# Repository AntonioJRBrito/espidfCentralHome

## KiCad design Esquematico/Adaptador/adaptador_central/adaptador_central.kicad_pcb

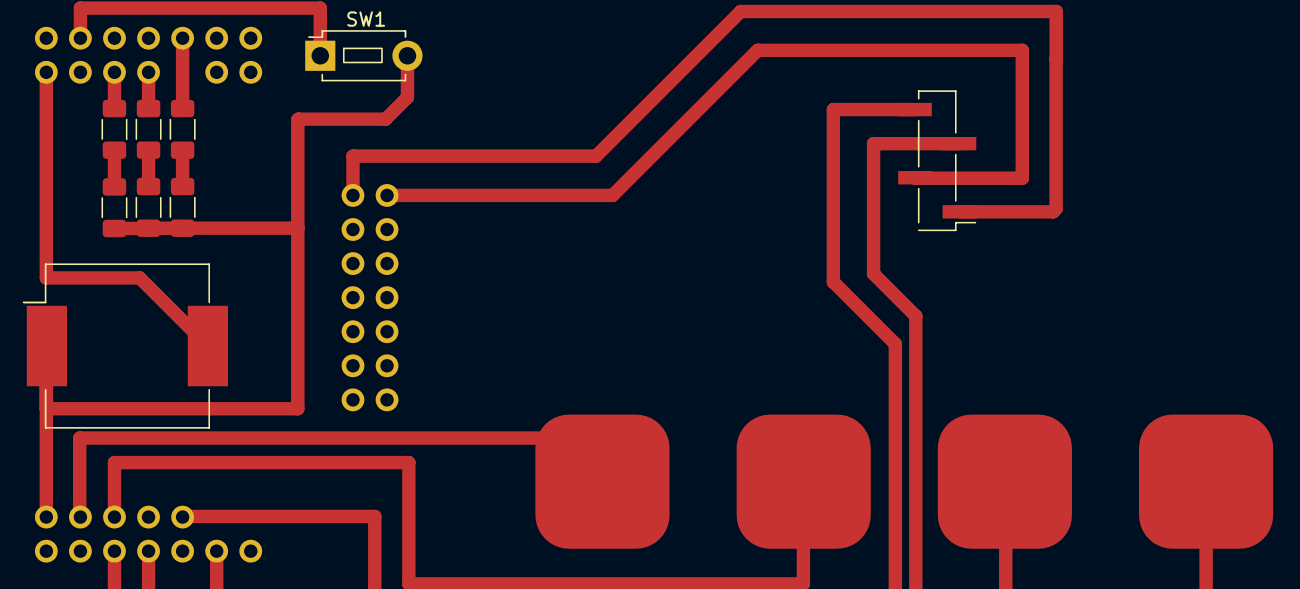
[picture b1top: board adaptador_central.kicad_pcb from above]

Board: 2 copper layers, 11 parts (0 on the bottom side), 16 nets.

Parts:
BZ1: Buzzer; Buzzer_Mallory_AST1240MLQ
Brd1: SSD1306; PinHeader_1x04_P2.54mm_Vertical_SMD_Pin1Left
D1, D2, D3: LED; R_1206_3216Metric_Pad1.30x1.75mm_HandSolder
Jtouch1: Conn_01x04_Pin; touch
R1, R2, R3: R; R_1206_3216Metric_Pad1.30x1.75mm_HandSolder
SW1: SW_MEC_5G; SW_PUSH_1P1T_6x3.5mm_H5.0_APEM_MJTP1250
U1: ESP32-S3-WROOM-1; ESP_S3_dual_suport

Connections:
unnamed: BZ1.1 (+), Brd1.2 (VCC), D1.2 (A), D2.2 (A), D3.2 (A), SW1.2 (A), U1.2 (3V3)
unnamed: BZ1.2 (-), U1.39 (GPIO1/TOUCH1/ADC1_CH0)
unnamed: Brd1.1 (GND), U1.1 (GND), U1.40 (GND)
unnamed: Brd1.3 (SCL), U1.11 (GPIO18/U1RXD/ADC2_CH7/CLK_OUT3)
unnamed: Brd1.4 (SDA), U1.10 (GPIO17/U1TXD/ADC2_CH6)
unnamed: D1.1 (K), R1.2
unnamed: D2.1 (K), R2.2
unnamed: D3.1 (K), R3.2
unnamed: Jtouch1.0 (Pin_1), U1.4 (GPIO4/TOUCH4/ADC1_CH3)
unnamed: Jtouch1.1 (Pin_2), U1.6 (GPIO6/TOUCH6/ADC1_CH5)
unnamed: Jtouch1.2 (Pin_3), U1.7 (GPIO7/TOUCH7/ADC1_CH6)
unnamed: Jtouch1.3 (Pin_4), U1.5 (GPIO5/TOUCH5/ADC1_CH4)
unnamed: SW1.1 (A), U1.38 (GPIO2/TOUCH2/ADC1_CH1)
unnamed: R3.1, U1.32 (MTCK/GPIO39/CLK_OUT3/SUBSPICS1)
unnamed: R2.1, U1.33 (MTDO/GPIO40/CLK_OUT2)
unnamed: R1.1, U1.35 (MTMS/GPIO42)

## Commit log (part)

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2025-10-23 Commit inicial do projeto CentralHome
2025-10-23 Alterado o main
2025-10-23 Commit automático
2026-01-13 Reenvio completo do projeto
2026-03-19 new update
